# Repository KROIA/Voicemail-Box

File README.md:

# Voicemail-Box

## About
Modern-day communication is more and more reliant on smartphones. This can cause issues in numerous situations. It can alienate people with writing, seeing, or technological deficiencies. 

Since the development of new electronic systems is often too complicated for non-affine people, the goal is to develop a platform that makes it easier to get started with such a project. The highest priority was given to audio input and output, user differentiation/management, file saving, and transferring those wirelessly.

<tr>
<td>
<div align="center">
     
</div>
</td>

---
## Repository overview
The repository is structured the following way:
- **Hardware** folder contains the hardware specific project.  
[Go to Hardware Dokumentation](Hardware/README.md)

- **Software** folder contains the main source code and api.  
[Go to Software Dokumentation](Software/BSP_VoiceMailBox/README.md)

---
## Features
The Voicemailbox Development Platform offers the basic hardware and software components to develop specific use cases out of it.
The custom PCB is designed to be flexible for different kind of configurations and the software is built in a modular and structural way, using modern C++ to be able to abstract hardware components better and make it easy to develop custom business logic on to it.

### The current state of development features the following:
- Recording audio from different sources:
  - Audio jack for left and right audio channel.
  - Built-in microphone
- Playback audio to the audio output jack
- Filesystem using a SD-Card and easy to use file class for reading and writing files
- Two different audio encodings for files are supported:
  - **WAV** Which is a lossless easy to write/read file format for audio data with the downside of beeing very large in filesize.
  - **MP3** Which is a more common used audio format, much more compressed and the prefered choice for a application such as this one.
            The only downside is, that it is not fully supported on a **M7** core.
- Testserver implementation that manages file upload/download.
  With the help of the ESP32, files can be uploaded/downloaded from a server using a WIFI connection.
  No user authentication is implemented at the current state of the development.
- Two free programmable LED's.
- Four free programmable buttons.
- Two free programmable analog inputs.
  
### Untested features:
- Playback using the speaker connection (J603) is implemented in hardware but not implemented and tested in the software.
- NFC module

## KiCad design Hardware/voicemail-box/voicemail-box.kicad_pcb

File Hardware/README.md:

# Hardware
This folder contains all HW-Files and documentation of how to use them

## Info
The name for the Microcontroller/Evaluation Boards will be abreviated in the instructions as the following:
- Voicemail-Box Board: 	VMBB
- STM32F469-Disco:		F469
- Nucleo-H755:			H755
- X-Nucleo NFC8:		NFC8
- P-Mod ESP32:			PMOD
- ...

## Orientation
All jumper/switch settings asume that the board is orientet like this image unless otherwise specified.   

Here is a schematic view where jumpers are also labled:  

## HW Setup
The VMBB is made to be soldered in a full and a partial configuration as well as beeing compatible with
multiple Microcontrollerboards (F469 and H755)

The partial configuration is made for people that are inexperienced with soldering / are lacking equipment.  

The full configuration is made as the de-facto correct way of manufacturing at the cost off beeing way more difficult to produce.

> [!CAUTION]  
> When fully soldering the NFC part will likely require a microscope  
> and the Wifi part will require an aditional USB to UART Converter with 3.3V logic level write the flash memory of ESP32.

to use one or the other, select the correct BOM to solder and only solder the mentioned parts. There are no differences in the use of the finished board.

- tbd: make the BOMs and a assembly plan
- tbd: add pictures

### Soldering
- [Go to partial BOM](PCB/BOM/voicemail-box_partial.csv)
- [Go to full BOM](PCB/BOM/voicemail-box_full.csv)

> [!NOTE]  
> If you want to edit the PCB files I recommend using KICAD with the KiVar Plugin

## Select Microcontroller Board in use (get the correct Jumper settings)
- [Configure Board for H755](Config/H755/H755.md)
- [Configure Board for F469](Config/F469/F469.md)

## Configure periperal Conections (for those which offer this feature)
Some devices can use different Connection Interfaces offereing different benefits.
This is due to the fact, that this is an development board.  
In a specific use, you would select one and ignore the other one.

## WLAN/BLE
Wireless connection can be made either through UART or SPI  
While SPI is way faster, it is more complicated to set up
- [Configure WLAN/BLE using SPI](Config/SPI_WLAN.md)
- [Configure WLAN/BLE using UART](Config/UART_WLAN.md)
## NFC
NFC can be read-out either through I2C or SPI  
While SPI is way faster and is tested.
I2C would help in case that there is a pin-limitation of the final project.
- F469
    - [Configure NFC using SPI](Config/F469/NFC_SPI_F469.md)
    - [Configure NFC using I2C](Config/F469/NFC_I2C_F469.md) 
- H755
    - [Configure NFC using SPI](Config/H755/NFC_SPI_H755.md)
    - [Configure NFC using I2C](Config/H755/NFC_I2C_H755.md) 

## Configure HW Features
- [Configure PSU](Config/PSU.md)
- [Configure Poti](Config/Poti.md)
- [Configure Audio](Config/Audio.md)
- [Configure LEDs](Config/Leds.md)
- [Configure Buttons](Config/Buttons.md)
- [Configure micro SD](Config/uSD.md)

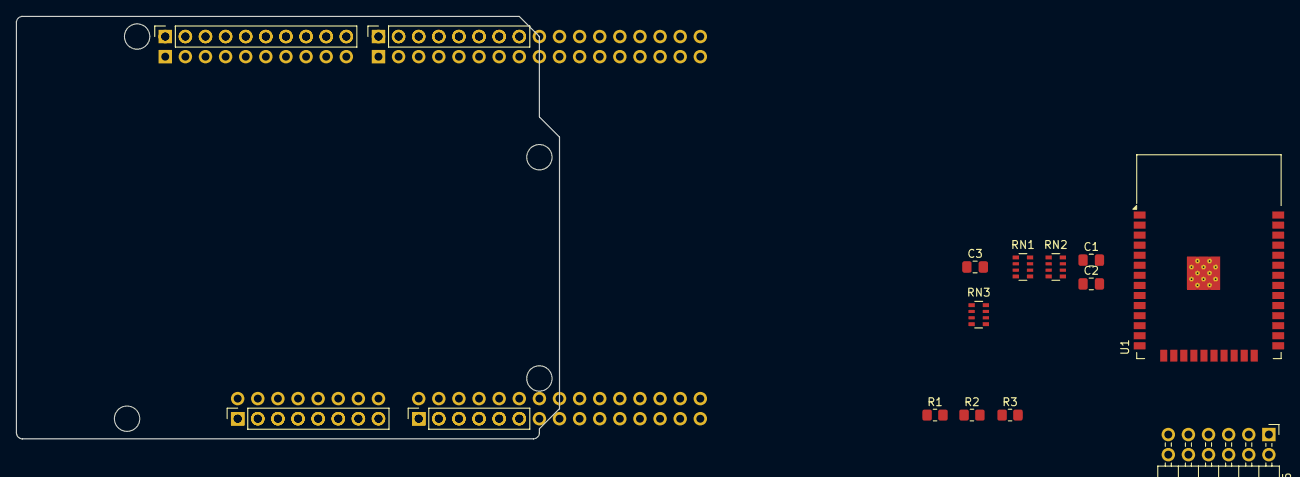
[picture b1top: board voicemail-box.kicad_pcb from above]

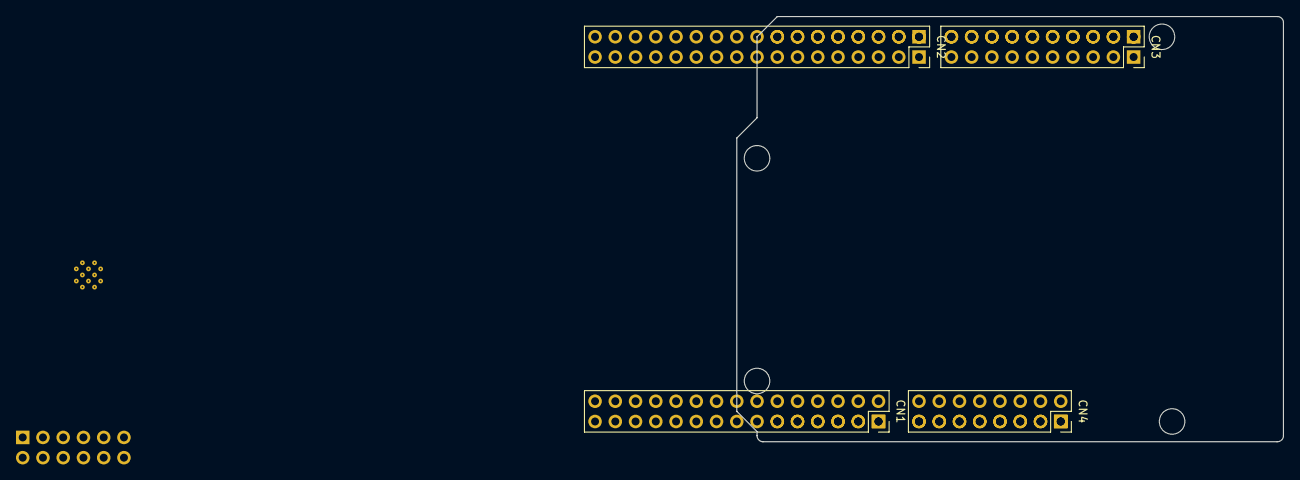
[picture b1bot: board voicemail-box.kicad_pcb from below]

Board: 2 copper layers, 68.6 x 53.3 mm, 23 parts (4 on the bottom side), 17 nets, no tracks yet.

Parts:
C1, C3: 100n; C_0805_2012Metric_Pad1.18x1.45mm_HandSolder
C2: 10u; C_0805_2012Metric_Pad1.18x1.45mm_HandSolder
CN1: PinSocket_2x15_P2.54mm_Vertical
CN2: PinSocket_2x17_P2.54mm_Vertical
CN3: PinSocket_2x10_P2.54mm_Vertical
CN4: PinSocket_2x08_P2.54mm_Vertical
J1: Power; PinSocket_1x08_P2.54mm_Vertical
J2: Digital/PWM; PinSocket_1x10_P2.54mm_Vertical
J3: Analog; PinSocket_1x06_P2.54mm_Vertical
J4: Digital/PWM; PinSocket_1x08_P2.54mm_Vertical
J5: Conn_02x06_Top_Bottom; PinHeader_2x06_P2.54mm_Horizontal
MH1, MH2, MH3, MH4: MountingHole_3.2mm
R1: 10k; R_0805_2012Metric_Pad1.20x1.40mm_HandSolder
R2: 20k; R_0805_2012Metric_Pad1.20x1.40mm_HandSolder
R3: 1k; R_0805_2012Metric_Pad1.20x1.40mm_HandSolder
RN1: np_0R; R_Array_Convex_4x0603
RN2: 0R; R_Array_Convex_4x0603
RN3: 10k; R_Array_Convex_4x0603
U1: ESP32-WROOM-32

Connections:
+3V3: C1.1, C2.1, C3.1, J1.2, J1.4, J5.6, J5.12, R1.1, R2.1, RN3.1 (R1.1), RN3.2 (R2.1), RN3.3 (R3.1), RN3.4 (R4.1), U1.2 (VDD)
/CTS/SCK: J5.4, RN1.1 (R1.1), RN2.1 (R1.1)
/EN: J5.8, R1.2, U1.3 (EN)
/GPIO: J5.10, U1.8 (IO32)
/INT: J5.7, U1.24 (IO2)
/IO0: R2.2, R3.1, U1.25 (IO0)
/MISO: RN2.7 (R2.2), U1.31 (IO19)
/MOSI: RN2.6 (R3.2), U1.37 (IO23)
/RTS/SS: J5.1, RN1.4 (R4.1), RN2.4 (R4.1)
/RXD: RN1.6 (R3.2), U1.27 (IO16)
/RXD/MOSI: J5.2, RN1.3 (R3.1), RN2.3 (R3.1)
/SCK: RN2.8 (R1.2), U1.30 (IO18)
/SELECT: J5.9, U1.11 (IO26)
/SS: RN2.5 (R4.2), U1.29 (IO5)
/TXD: RN1.7 (R2.2), U1.28 (IO17)
/TXD/MISO: J5.3, RN1.2 (R2.1), RN2.2 (R2.1)
GND: C1.2, C2.2, C3.2, J1.6, J1.7, J2.4, J5.5, J5.11, R3.2, U1.1 (GND), U1.15 (GND), U1.38 (GND), U1.39 (GND)

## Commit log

2025-02-26 Initial
2025-03-05 + Doku drawio files + Doku Board pdfs + NFC Sandbox Project + uSD Sandbox Project
2025-03-05 + Audio folder and info
2025-03-05 Create Readme.md
    Started Dokumentation
2025-03-05 Update README.md
    Started dokumentation
2025-03-05 Delete DevSandbox/Readme.md
    removed since copy
2025-03-05 ~ fixed NFC Example ~ started testing of MicroSD Example
2025-03-05 init
2025-03-06 SPI & UART Communication attempt
2025-03-07 Wifi AP via UART working
2025-03-07 + Micro SD Project based on STM32F469 - Micro SD Project based on NUCLEO-H755 + Timeplan drawio
2025-03-07 + audio example ~ timeplan
2025-03-11 start HW
2025-03-11 ~ Prios
2025-03-11 ~ PDF Export
2025-03-12 ~ Block-Diagrammaccording to meeting
2025-03-12 fixed files
2025-03-12 fixed pdf
2025-03-12 ~ Projektkriterien markiert
2025-03-12 + gitignore ~ added existing pinout of sandbox tests
2025-03-12 - old project
2025-03-12 + Setup sw Projects
    + LibVoiceMailBox
    Library for the project
    + VoiceMailBoxApplication
    Test enviroment Project for developing the library
2025-03-12 ~changed to hierarchical schematic
2025-03-12 + Class diagram
2025-03-19 + FAT32File class
2025-03-19 ~ HW Configuration
2025-03-19 First file IO
2025-03-23 + IServerClient
2025-03-24 + datasheets
2025-04-01 ~working on first pcb-Draft
2025-04-02 ~ WIFIServerClient
2025-04-02 + IAudioInputDevice
2025-04-02 - unused datasheets + new datasheets
2025-04-03 schematic draft
2025-04-03 + I2S basic configuration
2025-04-04 corrected pinout to nucleo description
2025-04-11 HW Layout progress todo: + Antenna + Audio Jacks + Planes (Supply only)
2025-04-16 layout progress step
2025-04-16 created project (not done)
2025-04-16 + CodecTest
    CodecTest: Project to test the audio codec.
    ~ ESP32_WIFI: Connecting to wifi, try to send data to a server (not working)
2025-04-16 ~Readme
2025-04-17 schema review
2025-04-23 ~layout
2025-04-25 state of pcb ordered
2025-05-05 + Nucleo144 Project for the Voicemail-Box Shield
    + Basic configuration for the Voicemail-Box Shield
    All changes in the IOC except clock config, can be found in the readme.md in the project folder
2025-05-07 HW Doku test
2025-05-07 tests for mermaid alignment
2025-05-07 working on Hw-Doku
2025-05-07 + F469Discovery_Application Project
    + clean to remove generated files
2025-05-07 + Comments
2025-05-07 ~feeddback config
2025-05-07 corrected textColor
2025-05-07 fix textcolor
2025-05-07 markdown with linking
2025-05-07 ~ splitt doku to multipla files
2025-05-07 doku started pinout todo
2025-05-07 Moved BSP outside of the project
    + Potentiometer readout
2025-05-07 + WIFI UART
    ~ UART is now working with DMA
    fast sending and receiving not working correctly yet.
2025-05-08 - Removed DMA for UART
    + I2S Configuration
2025-05-08 + Quick and dirty AudioCodec test impl
2025-05-09 + First working audio capture and live playback ^^
    - removed build dir "Debug"
2025-05-10 + Performance measurement for audio processing
    + gitignore for other stm projects
2025-05-10 + VMB_HAL Abstraction
2025-05-10 + File system
    + Audio recording example
2025-05-10 - Removed Debug build folders
2025-05-10 - Removed Debug folders
2025-05-12 + DBG Pins
    ~ UART
    + WaitUntil
    ~ Utils
    + TickCountInMS
2025-05-13 + Codedocumentation
2025-05-13 + First file upload to the test server
2025-05-16 - Removed unused projects
2025-05-16 ~ doku
2025-05-16 ~doku
2025-05-16 ~ Documentation
2025-05-17 + First file download
2025-05-18 + Test application for demo
2025-05-19 ~ Working Demo
2025-05-19 + MP3 class
    + MP3 encoder
2025-05-20 ~ Moved File.h and File.cpp to new location
2025-05-20 ~ Cleanup demo application
2025-05-20 + Documentation
2025-05-21 + First working MP3 decoder
2025-05-21 + Abstract
2025-05-21 + MP3 file compatibility
    + MP3File class
    + MP3_encoder class
    + MP3_decoder class
    ~ Changed the AudioPlayer and AudioRecorder to use the MP3 format.
2025-05-21 + pics ~doku
2025-05-21 ~ gitignore
2025-05-22 + Automatic update for updatable objects
    + Updatable interface
    ~ The internal usage of the leds can now be enabled or disabled in the settings.h
    ~ Internal debug prints can now be enabled or disabled in the settings.h -> this enables/disables the compilation of the Logger class completly
    ~ Changed the plarform interface to reduce the files, removed BSP_VoiceMailBox.cpp
    + Documentation
2025-05-23 ~ Connecting to wifi, set to station mode before connecting
2025-05-23 + simple microphone gain setup
2025-05-23 reorder Folderstructure
2025-05-23 + microphone input gain setting in the codec
2025-05-23 ~ Moved folders "DevSandbox" and "Demos" to "Software"
2025-05-24 ~ Moved I2C as private peripheral to a platform wide I2C instance
2025-05-26 ~ hw-files update
2025-05-26 + Initial H755 Example project but not configured correctly yet
2025-05-26 ~ Readme
2025-05-26 ~ Clean include paths
2025-05-26 + sdmmc but not working yet
2025-05-27 ~ changed include name for digitalPin.hpp
2025-05-27 ~proj files chaos fix
2025-05-27 First not working H755 Test ¯\(°_o)/¯
2025-05-27 ~ Changed StLink UART Baud to 115200
2025-05-27 ~ Restored dev demo application
2025-05-27 - sdmmc
2025-05-28 ~ Documentation
    + I2S image
2025-05-28 ~fixes on schematic and pcb ~prep for final output generation
2025-05-28 ~documentation
2025-05-29 ~ moved H755 example
2025-05-29 ~doku largely changed from mermaid to drawio
2025-05-29 ~flash part ESP32 started
2025-05-29 + F469 HelloAudio example
    ~ Moved demos to board specific folders
2025-05-29 ~ board 3D files improved ~ bom output prep
2025-05-30 + Demo for F469 RecordPlayback
2025-05-30 finaly working variants
2025-05-30 ~bom rem from ignore
2025-05-30 + F469 MultiExample that combines multiple examples in one project
2025-05-30 + AudioRecorder example
2025-05-30 + File and WAVFile example
2025-05-31 + MP3File example
2025-05-31 + I2C example
2025-05-31 + I2S example
2025-05-31 + MP3 Encoder/Decoder example
2025-05-31 + UART example
2025-05-31 + Audio codec DC offset calculation
2025-05-31 ~ Saving little memory for examples
2025-06-01 + Microphone DC offset autocorrection for the AudioCodec class
    + DC offset correction example
2025-06-02 ~typo
2025-06-02 + ATCommandClient & Codec example
    + TestServer
2025-06-02 updated folder-structure
2025-06-02 ~path
2025-06-02 rm debug data
2025-06-02 + assembly plan
2025-06-02 + Logger example & documentation
2025-06-02 ~assembly plan
2025-06-02 + Updatable example & documentation
2025-06-02 + Timer class, documentation & example
2025-06-03 - removed unused files
2025-06-03 ~fixed spelling
2025-06-03 - removed .settings folder
2025-06-04 fixed structure
2025-06-04 cleanup
2025-06-04 added part labeling
2025-06-05 Auto stash before merge of "main" and "origin/main"
2025-06-05 re-added step files for propper 3D view
2025-10-24 ~ Timer class
    + Added missing return in Timer::stop()
    + Doku in Timer.hpp
